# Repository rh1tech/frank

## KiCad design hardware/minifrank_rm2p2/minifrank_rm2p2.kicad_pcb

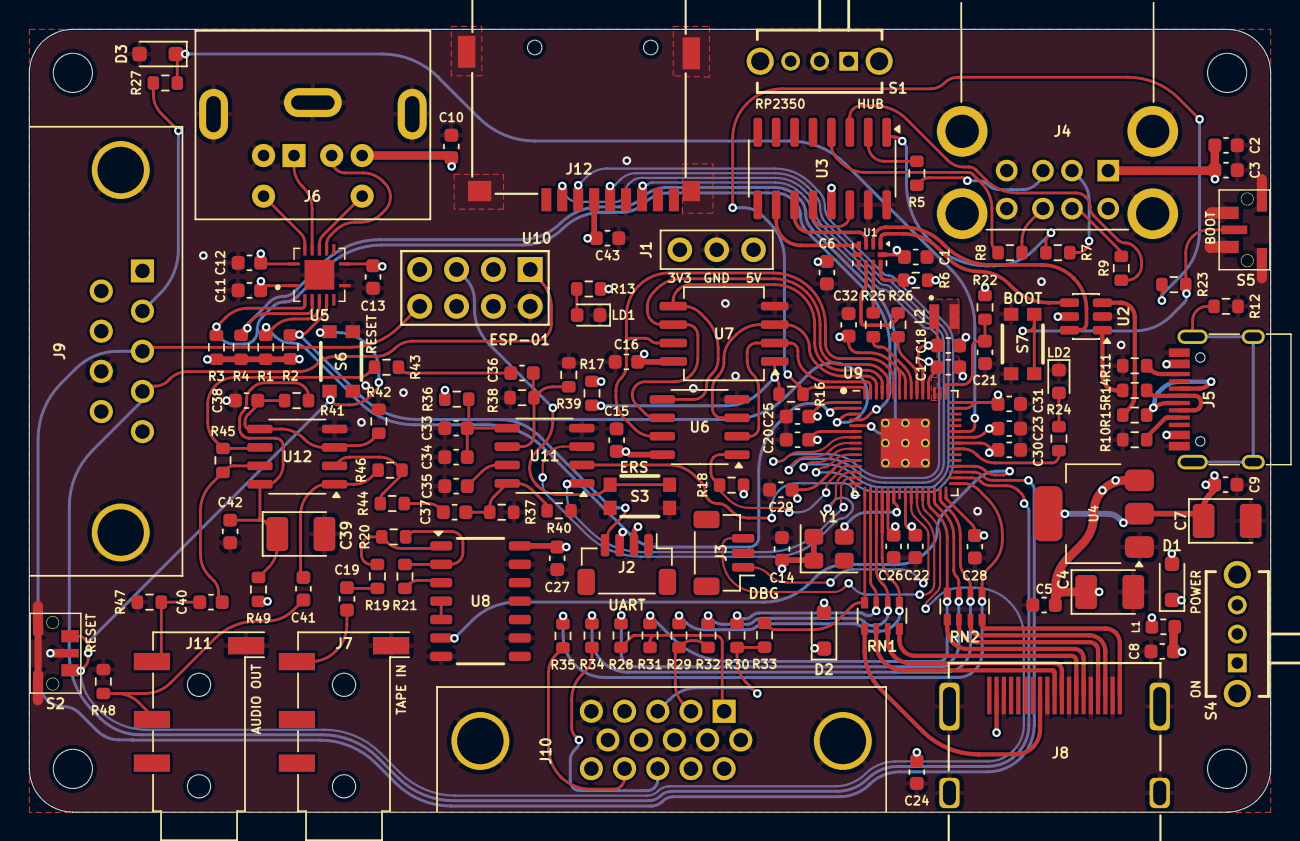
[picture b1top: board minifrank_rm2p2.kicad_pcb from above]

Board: 4 copper layers, 85.6 x 54.0 mm, 137 parts (0 on the bottom side), 113 nets.

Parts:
C1, C5, C8, C9, C10, C11, C12, C13, C14, C15, C16, C19, C20, C23, C24, C25, C26, C27, C28, C29, C30, C31, C32, C34, C42, C43: 100n; C_0603_1608Metric
C2, C3, C33, C35, C36, C37, C38, C40, C41: 10u; C_0603_1608Metric
C4, C7: 22u; Capacitor (3528, tantalum, polar)
C6, C17, C18, C21, C22: 4.7u; C_0603_1608Metric
C39: 10u; Capacitor (3528, tantalum, polar)
D1, D2: 1N5819WS; Diode (SOD-323)
D3: 3V3; Diode (SOD-323)
H1, H2, H3, H4: Hole 2.7mm; Mounting Hole (2.7mm)
J1: PWR; Pin Header (1x03)
J2: UART; JST_SH_BM04B-SRSS-TB_1x04-1MP_P1.00mm_Vertical
J3: DEBUG; JST_SH_BM03B-SRSS-TB_1x03-1MP_P1.00mm_Vertical
J4: SS-52100-004; USB Type A (stacked)
J5: USB4215-03-A; USB Type C
J6: MDC-036; MiniDIN (6 Pin, female)
J7, J11: PJ-320D; Jack (3.5mm, PJ-320D)
J8: DC3RX19JA2; HDMI (female)
J9: GP2; D-SUB (9 pin, male, top mount)
J10: VGA; D-SUB (15 pin, female)
J12: 104031-0811; MicroSD (SMD, long)
L1: 330R; L_0603_1608Metric
L2: 3.3u; L_pol_2016
LD1: Green; LED_0603_1608Metric
LD2: Blue; LED_0603_1608Metric
R1, R2, R3, R4, R6, R17, R18, R39, R40, R41, R42, R43, R44: 10K; R_0603_1608Metric
R5, R7, R8, R9, R14, R15: 22R; R_0603_1608Metric
R10, R11: 5.1K; R_0603_1608Metric
R12: 1M; R_0603_1608Metric
R13, R23, R24, R27, R31, R32, R33: 1K; R_0603_1608Metric
R16: 0R; R_0603_1608Metric
R19: 4.7K; R_0603_1608Metric
R20, R21: 100K; R_0603_1608Metric
R22: 33R; R_0603_1608Metric
R25, R26: 27R; R_0603_1608Metric
R28, R29, R30: 330R; R_0603_1608Metric
R34, R35, R36, R49: 100R; R_0603_1608Metric
R37, R38: 470R; R_0603_1608Metric
R45, R46: 47K; R_0603_1608Metric
R47, R48: 20K; R_0603_1608Metric
RN1, RN2: 270R; Resistor Array (4x0603)
S1, S4: SK12D07VG3NS
S2, S5: RP Reset; TS-1234VW
S3: ESP Reset; KMR_2
S6, S7: RP Reset; KMR_2
U1: TS3USB221RSER; UQFN-10
U2: USBLC6-2SC6; SOT-23-6
U3: MW7211A; SOP-16
U4: NCP1117-3.3_SOT223; SOT-223-3_TabPin2
U5: TXS0104ERGYR; RGY_S-PVQFN-N14_
U6: ESP-PSRAM32; SO-8
U7: W25Q128JVS; SOIC-8
U8: CD4069UBM; SOIC127P600X175-14N
U9: RP2350; QFN 60 (RP2350A)
U10: ESP-01v090; ESP-01
U11: TDA1387T; SO-8
U12: LM358; SO-8
Y1: ASE-12MHz; Oscillator_SMD_Abracon_ASE-4Pin_3.2x2.5mm

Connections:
+1V1: C18.1, C20.1, C22.1, C23.1, L2.1, U9.6 (DVDD), U9.23 (DVDD), U9.39 (DVDD), U9.50 (VREG_FB)
+3V3: C1.2, C7.1, C9.2, C11.1, C13.1, C14.1, C15.1, C16.1, C17.1, C25.1, C26.1, C27.1, C28.1, C29.1, C30.1, C31.1, C32.1, C43.2, J1.1, J2.2, J12.4 (VDD), R1.2, R2.2, R3.2, R4.2, R6.1, R13.2, R17.1, R18.2, R22.1, U1.10 (VCC), U4.2 (VO), U5.1 (VCCA), U5.8 (OE), U6.8 (VCC), U7.8 (VCC), U8.14 (VDD), U9.1 (IOVDD), U9.11 (IOVDD), U9.20 (IOVDD), U9.30 (IOVDD), U9.38 (IOVDD), U9.44 (ADC_AVDD), U9.45 (IOVDD), U9.49 (VREG_VIN), U9.53 (USB_OTP_VDD), U9.54 (QSPI_IOVDD), U10.7 (VCC), Y1.1 (EN), Y1.4 (Vdd)
/Audio/AMP_OUTL: C40.2, J11.T, R47.2
/Audio/AMP_OUTR: C41.2, J11.R, R48.2
/Audio/TDA_L: C36.1, R38.2, R39.1, U11.6 (A_LEFT)
/Audio/TDA_R: C37.1, R37.1, R40.1, U11.8 (A_RIGHT)
/D+: R25.1, U1.8 (D+)
/D-: R26.1, U1.7 (D-)
/ESP_RST: S3.2, S3.4, U10.5 (RST)
/GPIO0: J2.3, R1.1, U5.4 (A3), U9.2 (GPIO0)
/GPIO1: J2.4, R2.1, U5.5 (A4), U9.3 (GPIO1)
/GPIO2: R3.1, U5.2 (A1), U9.4 (GPIO2)
/GPIO3: R4.1, U5.3 (A2), U9.5 (GPIO3)
/GPIO4: J12.7 (DAT0), U9.7 (GPIO4)
/GPIO5: J12.2 (DAT3/CD), U9.8 (GPIO5)
/GPIO6: J12.5 (CLK), U9.9 (GPIO6)
/GPIO7: J12.3 (CMD), U9.10 (GPIO7)
/GPIO8: R18.1, U6.1 (~CE), U9.12 (GPIO8)
/GPIO9: U9.13 (GPIO9), U11.3 (DATA)
/GPIO10: U9.14 (GPIO10), U11.1 (SCLK)
/GPIO11: U9.15 (GPIO11), U11.2 (LRCK)
/GPIO12: R33.1, RN1.4 (R4.1), U9.16 (GPIO12)
/GPIO13: R30.1, RN1.3 (R3.1), U9.17 (GPIO13)
/GPIO14: R32.1, RN1.2 (R2.1), U9.18 (GPIO14)
/GPIO15: R29.1, RN1.1 (R1.1), U9.19 (GPIO15)
/GPIO16: R31.1, RN2.4 (R4.1), U9.27 (GPIO16)
/GPIO17: R28.1, RN2.3 (R3.1), U9.28 (GPIO17)
/GPIO18: R34.2, RN2.2 (R2.1), U9.29 (GPIO18)
/GPIO19: R35.2, RN2.1 (R1.1), U9.31 (GPIO19)
/GPIO20: J9.4, U9.32 (GPIO20), U10.1 (UTXD)
/GPIO21: J9.3, U9.33 (GPIO21), U10.8 (URXD)
/GPIO22: U8.6 (I=*C), U9.34 (GPIO22)
/GPIO26: D3.1 (K), R27.1, U9.40 (GPIO26_ADC0)
/PS2/KB_CLK_5V: J6.5, U5.13 (B1)
/PS2/KB_DATA_5V: J6.1, U5.12 (B2)
/PS2/MS_CLK_5V: J6.6, U5.11 (B3)
/PS2/MS_DATA_5V: J6.2, U5.10 (B4)
/Power/D1+: U1.1 (1D+), U2.4 (I/O2)
/Power/D1-: U1.2 (1D-), U2.6 (I/O1)
/Power/D2+: U1.3 (2D+), U3.11 (DPU)
/Power/D2-: U1.4 (2D-), U3.10 (DMU)
/Power/DS1+: R5.1, U3.2 (DP0)
/Power/DS1-: R7.1, U3.1 (DM0)
/Power/DS2+: R8.1, U3.4 (DP1)
/Power/DS2-: R9.1, U3.3 (DM1)
/Power/VBUS_IN: D1.1 (K), S4.2
/RP2350A/FLASH_SS: R16.2, R17.2, U7.1 (~CS)
/RP2350A/QSPI_SCLK: U6.6 (SCLK), U7.6 (CLK), U9.56 (QSPI_SCLK)
/RP2350A/QSPI_SD0: U6.5 (SI/SIO), U7.5 (DI(IO0)), U9.57 (QSPI_SD0)
/RP2350A/QSPI_SD1: U6.2 (SO/SIO), U7.2 (DO(IO1)), U9.59 (QSPI_SD1)
/RP2350A/QSPI_SD2: U6.3 (SIO2), U7.3 (IO2), U9.58 (QSPI_SD2)
/RP2350A/QSPI_SD3: U6.7 (SIO3), U7.7 (IO3), U9.55 (QSPI_SD3)
/RP2350A/QSPI_SS: R16.1, R23.1, U9.60 (QSPI_SS)
/RP2350A/VREG_AVDD: C21.1, R22.2, U9.46 (VREG_AVDD)
/RP2350A/VREG_LX: L2.2, U9.48 (VREG_LX)
/RP2350A/XIN: U9.21 (XIN), Y1.3 (OUT)
/RP2350A/~USB_BOOT: R23.2, S5.2, S7.2, S7.4
/RUN: S2.1, S6.2, S6.4, U9.26 (RUN)
/SWCLK: J3.1, U9.24 (SWCLK)
/SWD: J3.3, U9.25 (SWD)
/Tape In/TAPE: C19.2, J7.T
/USBSW: R6.2, S1.3, U1.9 (S)
GND: C1.1, C2.2, C3.2, C4.2, C5.1, C6.2, C7.2, C8.2, C9.1, C10.2, C11.2, C12.2, C13.2, C14.2, C15.2, C16.2, C17.2, C18.2, C20.2, C21.2, C22.2, C23.2, C24.2, C25.2, C26.2, C27.2, C28.2, C29.2, C30.2, C31.2, C32.2, C33.2, C34.2, C35.2, C38.1, C39.2, C42.1, C43.1, D3.2 (A), J1.2, J2.1, J3.2, J4.4 (GND1), J4.8 (GND2), J4.9 (Shield), J5.1 (GND), J5.12 (GND), J6.3, J7.S, J8.2 (G_D2), J8.5 (G_D1), J8.8 (G_D0), J8.11 (G_CLK), J8.17 (G_DDC/CEC), J8.20 (SHIELD1), J8.21 (SHIELD2), J8.22 (SHIELD3), J8.23 (SHIELD4), J9.8, J10.0, J10.5, J10.6, J10.7, J10.8, J10.10, J11.S, J12.6 (VSS), LD1.1 (K), LD2.1 (K), R10.1, R11.1, R12.2, R37.2, R38.1, R39.2, R40.2, R42.1, R47.1, R48.1, S1.2, S2.2, S2.3 (GND), S3.1, S3.3, S5.1, S5.3 (GND), S6.1, S6.3, S7.1, S7.3, U1.5 (GND), U1.6 (~OE), U2.2 (GND), U3.15 (GND), U3.16 (GND), U4.1 (GND), U5.7 (GND), U5.15 (THERMAL_PAD), U6.4 (VSS), U7.4 (GND), U8.7 (VSS), U8.9 (D14), U8.11 (E), U8.13 (F), U9.47 (VREG_PGND), U9.61 (GND), U10.2 (GND), U11.4 (AGND), U12.4 (V-), Y1.2 (GND)
GPIO25: R24.2, U9.37 (GPIO25)
unnamed: C8.1, L1.2, S4.1
unnamed: C19.1, R19.2
unnamed: C36.2, R43.2
unnamed: C37.2, R44.2
unnamed: C40.1, R45.1, U12.7
unnamed: C41.1, R46.1, U12.1
unnamed: D1.2 (A), J5.2 (VBUS), J5.11 (VBUS)
unnamed: C24.1, D2.1 (K), J8.18 (+5V)
unnamed: J4.3 (D1+), R5.2
unnamed: J4.2 (D1-), R7.2
unnamed: J4.7 (D2+), R8.2
unnamed: J4.6 (D2-), R9.2
unnamed: J5.4 (CC1), R10.2
unnamed: J5.10 (CC2), R11.2
unnamed: J5.5 (DN2), J5.7 (DN1), R14.2
unnamed: J5.6 (DP1), J5.8 (DP2), R15.2
unnamed: J5.13 (SHIELD), R12.1
unnamed: J8.12 (CLKN), RN1.5 (R4.2)
unnamed: J8.10 (CLKP), RN1.6 (R3.2)
unnamed: J8.9 (D0N), RN1.7 (R2.2)
unnamed: J8.7 (D0P), RN1.8 (R1.2)
unnamed: J8.6 (D1N), RN2.5 (R4.2)
unnamed: J8.4 (D1P), RN2.6 (R3.2)
unnamed: J8.3 (D2N), RN2.7 (R2.2)
unnamed: J8.1 (D2P), RN2.8 (R1.2)
unnamed: J9.2, R27.2
unnamed: J10.1, R28.2, R31.2
unnamed: J10.2, R29.2, R32.2
unnamed: J10.3, R30.2, R33.2
unnamed: J10.13, R34.1
unnamed: J10.14, R35.1
unnamed: LD1.2 (A), R13.1
unnamed: LD2.2 (A), R24.1
unnamed: R14.1, U2.1 (I/O1)
unnamed: R15.1, U2.3 (I/O2)
unnamed: U3.12 (VD33), U3.14 (VD3)
unnamed: R19.1, R20.2, U8.1 (A)
unnamed: R21.1, U8.3 (B)
unnamed: U8.4 (H=*B), U8.5 (C)
unnamed: R20.1, R21.2, U8.2 (G-*A)
unnamed: R26.2, U9.51 (USB_DM)
unnamed: R25.2, U9.52 (USB_DP)
unnamed: C35.1, U11.7 (FLT)
unnamed: C33.1, C34.1, R36.1, U11.5 (VA)
unnamed: C38.2, R41.1, R42.2, U12.3 (+), U12.5 (+)
unnamed: R44.1, R46.2, U12.2 (-)
unnamed: R43.1, R45.2, U12.6 (-)
unnamed: C39.1, C42.2, R41.2, R49.2, U12.8 (V+)
VBUS: C2.1, C3.1, C4.1, C5.2, C6.1, C10.1, C12.1, D2.2 (A), J1.3, J4.1 (VBUS1), J4.5 (VBUS2), J6.4, J9.6, L1.1, R36.2, R49.1, U2.5 (VBUS), U3.13 (VDD5), U4.3 (VI), U5.14 (VCCB)

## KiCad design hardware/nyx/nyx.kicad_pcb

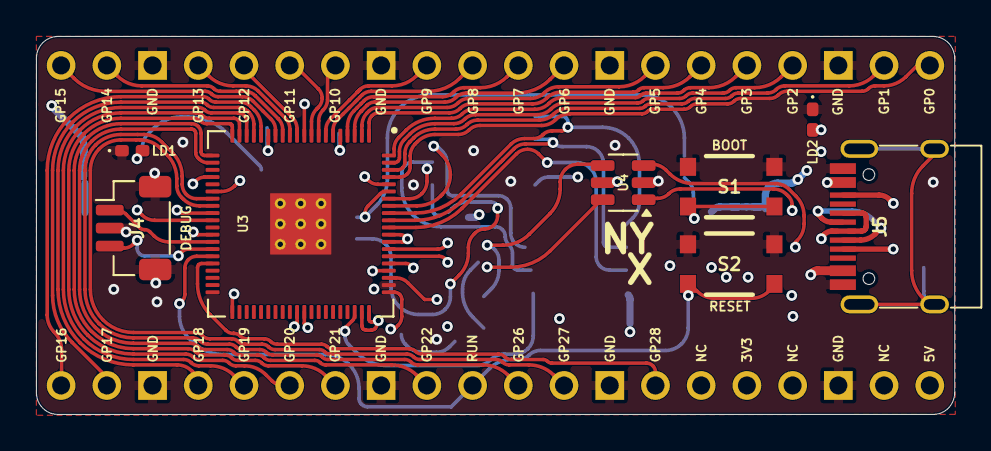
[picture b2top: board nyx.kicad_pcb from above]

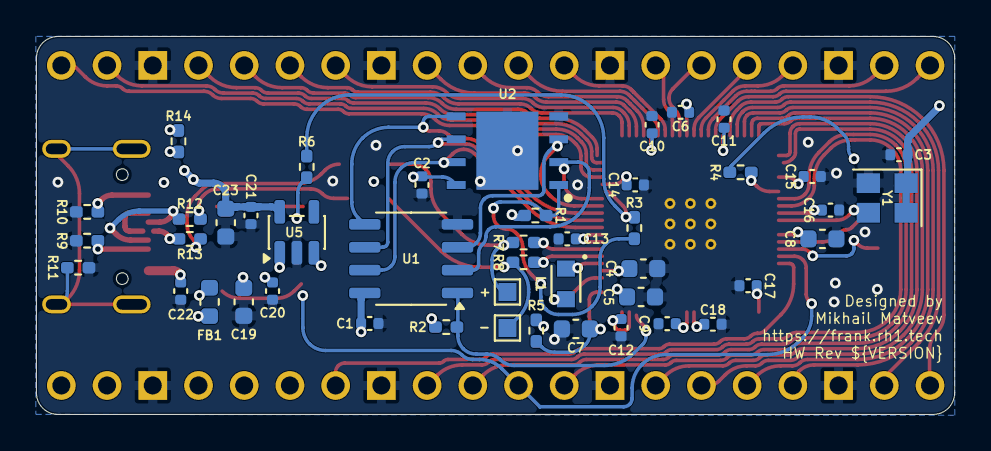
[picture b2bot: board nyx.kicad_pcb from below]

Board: 4 copper layers, 51.0 x 21.0 mm, 54 parts (44 on the bottom side), 61 nets.

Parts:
C1, C2, C3, C6, C9, C10, C11, C12, C13, C14, C15, C16, C17, C18, C20, C21, C22: 100n; C_0402_1005Metric
C4, C5, C7, C8: 4.7u; C_0603_1608Metric
C19, C23: 10u; C_0603_1608Metric
FB1: 330R; L_0603_1608Metric
J1: CON_PICO_21-40
J2: TestPoint_Pad_1.0x1.0mm_x2
J3: CON_PICO_1-20
J4: Debug; JST_SH_1x03_P1.00mm_Vertical
J5: USB4215-03-A; USB_C_Receptacle
L1: 3.3u; L_LQH2MCN100K02L
LD1: Blue; LED_0402_1005Metric
LD2: Green; LED_0402_1005Metric
R1, R2: 10K; R_0402_1005Metric
R3: 0R; R_0402_1005Metric
R4, R6, R14: 1K; R_0402_1005Metric
R5: 33R; R_0402_1005Metric
R7, R8: 27R; R_0402_1005Metric
R9, R10: 5.1K; R_0402_1005Metric
R11: 1M; R_0402_1005Metric
R12, R13: 22R; R_0402_1005Metric
S1: Boot; Button_SMD_3x4x2mm
S2: RP Reset; Button_SMD_3x4x2mm
U1: ESP-PSRAM64; SO-8_3.9x4.9mm_P1.27mm
U2: W25Q128JVPIQ; SON127P600X500X80-9N-D
U3: RP2350B; RP2350-QFN-80_10x10_P0.4mm
U4: USBLC6-2SC6; SOT-23-6
U5: ME6211C33M5; SOT-23-5
Y1: ASE-12MHz; Oscillator_SMD_3225_4Pin

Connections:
+1V1: C5.1, C6.1, C8.1, C9.1, L1.1, U3.10 (DVDD), U3.32 (DVDD), U3.51 (DVDD), U3.65 (VREG_FB)
+3V3: C1.1, C2.1, C3.1, C4.1, C10.1, C11.1, C12.1, C13.1, C14.1, C15.1, C16.1, C17.1, C18.1, C21.1, C23.1, J1.36, R1.2, R2.2, R5.1, R14.2, U1.8 (VCC), U2.8 (VCC), U3.5 (IOVDD), U3.15 (IOVDD), U3.24 (IOVDD), U3.29 (IOVDD), U3.41 (IOVDD), U3.50 (IOVDD), U3.59 (ADC_AVDD), U3.60 (IOVDD), U3.64 (VREG_VIN), U3.68 (USB_OTP_VDD), U3.69 (QSPI_IOVDD), U3.76 (IOVDD), U5.5 (V_{OUT}), Y1.1 (EN), Y1.4 (Vdd)
/D+: J2.1, R7.1, U4.4 (I/O2)
/D-: J2.2, R8.1, U4.6 (I/O1)
/GPIO0: J3.1, U3.77 (GPIO0)
/GPIO1: J3.2, U3.78 (GPIO1)
/GPIO2: J3.4, U3.79 (GPIO2)
/GPIO3: J3.5, U3.80 (GPIO3)
/GPIO4: J3.6, U3.1 (GPIO4)
/GPIO5: J3.7, U3.2 (GPIO5)
/GPIO6: J3.9, U3.3 (GPIO6)
/GPIO7: J3.10, U3.4 (GPIO7)
/GPIO8: J3.11, U3.6 (GPIO8)
/GPIO9: J3.12, U3.7 (GPIO9)
/GPIO10: J3.14, U3.8 (GPIO10)
/GPIO11: J3.15, U3.9 (GPIO11)
/GPIO12: J3.16, U3.11 (GPIO12)
/GPIO13: J3.17, U3.12 (GPIO13)
/GPIO14: J3.19, U3.13 (GPIO14)
/GPIO15: J3.20, U3.14 (GPIO15)
/GPIO16: J1.21, U3.16 (GPIO16)
/GPIO17: J1.22, U3.17 (GPIO17)
/GPIO18: J1.24, U3.18 (GPIO18)
/GPIO19: J1.25, U3.19 (GPIO19)
/GPIO20: J1.26, U3.20 (GPIO20)
/GPIO21: J1.27, U3.21 (GPIO21)
/GPIO22: J1.29, U3.22 (GPIO22)
/GPIO26: J1.31, U3.27 (GPIO26)
/GPIO27: J1.32, U3.28 (GPIO27)
/GPIO28: J1.34, U3.36 (GPIO28)
/Power/VBUS_IN: C22.1, FB1.1, J5.2 (VBUS), J5.11 (VBUS)
/RP2350B/GPIO47: R2.1, U1.1 (~CE), U3.58 (GPIO47_ADC7)
/RP2350B/QSPI_SCLK: U1.6 (SCLK), U2.6 (CLK), U3.71 (QSPI_SCLK)
/RP2350B/QSPI_SD0: U1.5 (SI/SIO), U2.5 (DI_(IO0)), U3.72 (QSPI_SD0)
/RP2350B/QSPI_SD1: U1.2 (SO/SIO), U2.2 (DO_(IO1)), U3.74 (QSPI_SD1)
/RP2350B/QSPI_SD2: U1.3 (SIO2), U2.3 (~WP_(IO2)), U3.73 (QSPI_SD2)
/RP2350B/QSPI_SD3: U1.7 (SIO3), U2.7 (~HOLD_OR_/RESET_(IO3)), U3.70 (QSPI_SD3)
/RP2350B/QSPI_SS: R3.1, R6.1, U3.75 (QSPI_SS)
/RP2350B/SWCLK: J4.3, U3.33 (SWCLK)
/RP2350B/SWD: J4.1, U3.34 (SWD)
/RP2350B/VREG_AVDD: C7.1, R5.2, U3.61 (VREG_AVDD)
/RP2350B/VREG_LX: L1.2, U3.63 (VREG_LX)
/RP2350B/XIN: U3.30 (XIN), Y1.3 (OUT)
/RP2350B/~USB_BOOT: R6.2, S1.1, S1.3
/RUN: J1.30, S2.1, S2.3, U3.35 (RUN)
GND: C1.2, C2.2, C3.2, C4.2, C5.2, C6.2, C7.2, C8.2, C9.2, C10.2, C11.2, C12.2, C13.2, C14.2, C15.2, C16.2, C17.2, C18.2, C19.1, C20.1, C21.2, C22.2, C23.2, J1.23, J1.28, J1.33, J1.38, J3.3, J3.8, J3.13, J3.18, J4.2, J5.1 (GND), J5.12 (GND), LD1.1 (K), LD2.1 (K), R9.1, R10.1, R11.2, S1.2, S1.4, S2.2, S2.4, U1.4 (VSS), U2.4 (GND_1), U2.9 (GND_2), U3.62 (VREG_PGND), U3.81 (GND), U4.2 (GND), U5.2 (V_{SS}), Y1.2 (GND)
unnamed: J5.4 (CC1), R9.2
unnamed: J5.10 (CC2), R10.2
unnamed: J5.5 (DN2), J5.7 (DN1), R12.2
unnamed: J5.6 (DP1), J5.8 (DP2), R13.2
unnamed: J5.13 (SHIELD), R11.1
unnamed: LD1.2 (A), R4.1
unnamed: LD2.2 (A), R14.1
unnamed: R12.1, U4.1 (I/O1)
unnamed: R13.1, U4.3 (I/O2)
unnamed: R1.1, R3.2, U2.1 (~CS)
unnamed: R4.2, U3.26 (GPIO25)
unnamed: R8.2, U3.66 (USB_DM)
unnamed: R7.2, U3.67 (USB_DP)
unnamed: C19.2, C20.2, FB1.2, U5.1 (V_{IN}), U5.3 (CE)
VBUS: J1.40, U4.5 (VBUS)

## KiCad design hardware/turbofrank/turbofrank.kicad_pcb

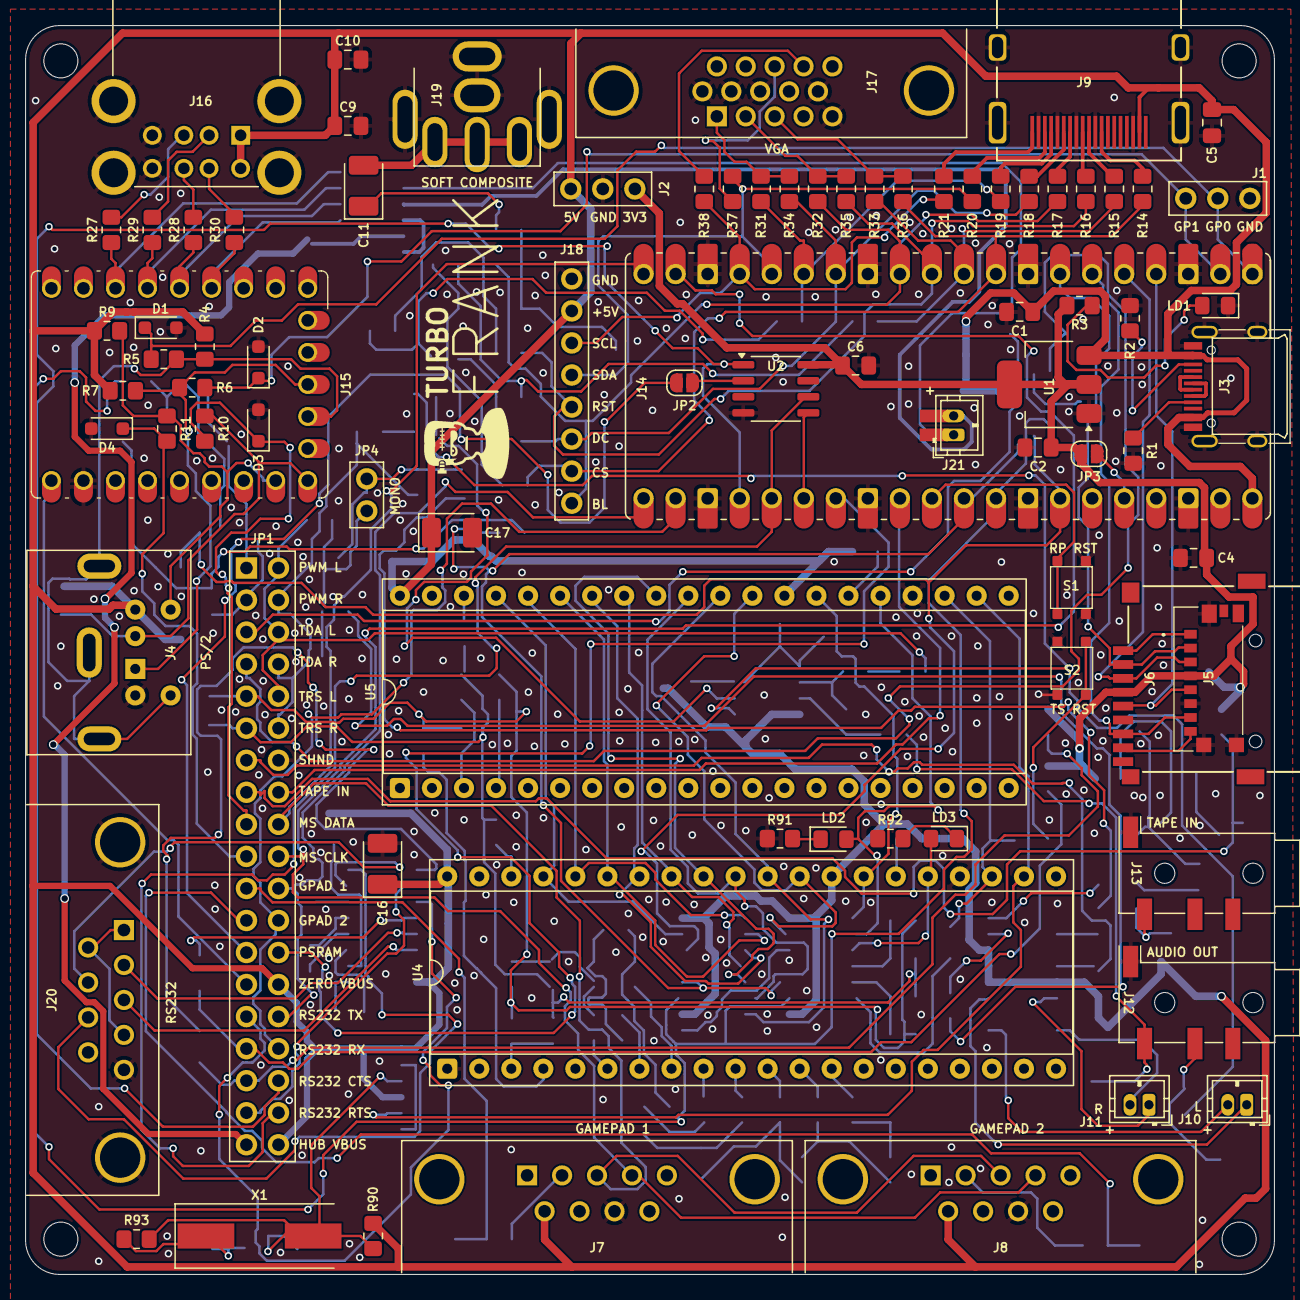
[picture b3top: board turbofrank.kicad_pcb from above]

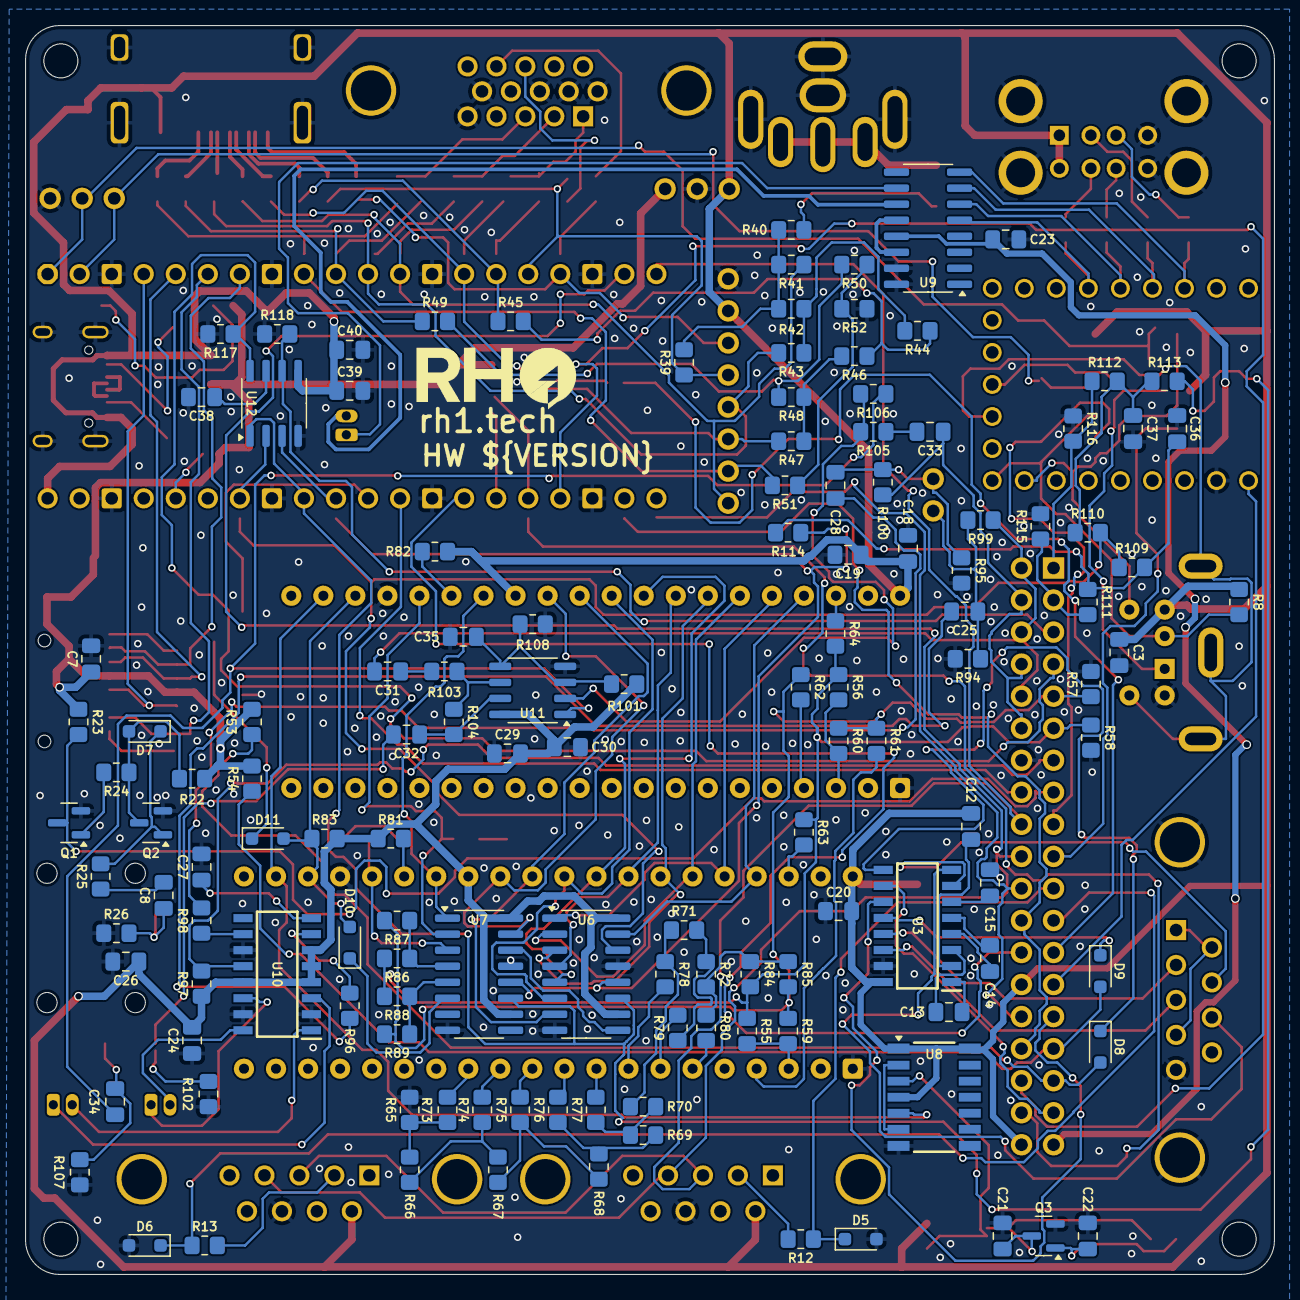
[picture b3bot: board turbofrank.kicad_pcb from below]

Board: 2 copper layers, 99.0 x 99.0 mm, 219 parts (132 on the bottom side), 187 nets.

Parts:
C1, C2, C9, C10, C29, C31, C32, C33, C34, C35, C38, C39: 10u; Capacitor (0805)
C3, C4, C5, C6, C7, C8, C18, C19, C20, C27, C30, C40: 100n; Capacitor (0805)
C11: 220u; Capacitor (3528, tantalum, polar)
C12, C13, C14, C15, C24, C25, C28: 1u; Capacitor (0805)
C16, C17: 100u; Capacitor (3528, tantalum, polar)
C21, C22: 22p; Capacitor (0805)
C23: 4.7u; Capacitor (0805)
C26: 47u; Capacitor (0805)
C36, C37: 47n; Capacitor (0805)
D1, D2, D3, D4, D5, D6: 3V3; Diode (SOD-323)
D7, D8, D9, D10, D11: 1N4148; Diode (SOD-323)
H1, H2, H3, H4: Hole 2.7mm; Mounting Hole (2.7mm)
J1: UART; Pin Header (1x03)
J2: PWR; Pin Header (1x03)
J3: USB4215; USB Type C
J4: MDC-036; MiniDIN (6 Pin, female)
J5: 0475710001; MicroSD (SMD, short)
J6: 104031-0811; MicroSD (SMD, long)
J7, J8, J20: D-SUB 9 Male; D-SUB (9 pin, male, top mount)
J9: DC3RX19JA2; HDMI (female)
J10: PAM L; Connector Female ZH 1.50mm (2 pins)
J11: PAM R; Connector Female ZH 1.50mm (2 pins)
J12, J13: PJ-320D; Jack (3.5mm, PJ-320D)
J14: Rasberry Pi Pico; Raspberry Pi Pico
J15: RP2040-Zero; Raspberry Pi Zero
J16: SS-52100-004; USB Type A (stacked)
J17: D-SUB 15 Female; D-SUB (15 pin, female)
J18: Pin Header 1x08; Pin Header (1x08)
J19: RCA-103; RCA
J21: USB HUB Data; Connector Female ZH 1.50mm (2 pins + tracks)
JP1: Main Jumper Set; Pin Header (2x19)
JP2, JP3: Jumper (Solder); Jumper (solder)
JP4: Mono; Pin Header (1x02)
LD1: Green; LED (0805)
LD2, LD3: Orange; LED (0805)
Q1, Q2, Q3: BC850; SOT-23
R1, R2: 5.1K; Resistor (0805)
R3, R4, R7, R8, R9, R12, R13, R23, R34, R35, R36, R53, R54, R66, R67, R68, R69, R70, R71, R72, R81, R82, R90, R91, R92, R113, R114: 1K; Resistor (0805)
R5, R6, R10, R11, R26, R37, R38: 100R; Resistor (0805)
R14, R15, R16, R17, R18, R19, R20, R21, R41, R43, R45, R47, R49, R51: 270R; Resistor (0805)
R22, R24, R25, R83, R84, R85, R86, R87, R88, R89, R96, R97, R98, R99, R100, R101, R103, R105, R108, R111, R112: 10K; Resistor (0805)
R27, R28, R29, R30: 22R; Resistor (0805)
R31, R32, R33: 330R; Resistor (0805)
R39: 750R; Resistor (0805)
R40: 51R; Resistor (0805)
R42, R44, R46, R48, R50: 150R; Resistor (0805)
R52: 300R; Resistor (0805)
R55, R56, R61, R62, R65, R73, R74, R75, R76, R77, R78, R79, R80, R94, R95, R109, R110, R115, R116: 2K; Resistor (0805)
R57, R58: 120R; Resistor (0805)
R59, R60, R63, R64: 4.7K; Resistor (0805)
R93: 100K; Resistor (0805)
R102, R107: 20K; Resistor (0805)
R104, R106: 47K; Resistor (0805)
R117, R118: 470R; Resistor (0805)
S1: TS-1233; Button (SMD, 3x3mm, 1-1)
S2: KLS7-TS3302; Button (SMD, 3x3mm, 1-1)
U1: NCP1117 3.3; SOT-223
U2: ESP-PSRAM32; SO-8
U3: MAX232CSE+; SOIC127P600X175-16N
U4, U5: JFC95101; DIP-40 (Socket)
U6, U7: 74HC595; SOP-16
U8: 74HC74; 74HCT74D
U9: MW7211A; SOP-16
U10: PAM8403D; SOIC127P600X175-16N
U11: LM358; SO-8
U12: TDA1387T; SO-8
X1: 3.58 MHz; Crystal (HC49-S)

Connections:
+3V3: C2.1, C4.2, C6.1, C7.1, J2.1, J5.P4 (VDD), J6.4 (VDD), JP3.2 (B), R3.2, R22.1, R23.1, R53.2, R54.2, U1.2 (VO), U2.8 (VCC)
/AMP_IN_L: C31.1, JP1.2, JP1.6, JP1.10, R99.1
/AMP_IN_R: C33.1, JP1.4, JP1.8, JP1.12, R100.1
/Audio Out/AMP_OUTL: C32.2, J12.T, R102.2
/Audio Out/AMP_OUTR: C34.2, J12.R, R107.2
/Audio Out/AMP_PAM_OUTL_M: J10.2, U10.3 (-OUTL)
/Audio Out/AMP_PAM_OUTL_P: J10.1, U10.1 (+OUT_L)
/Audio Out/AMP_PAM_OUTR_M: J11.2, U10.14 (-OUT_R)
/Audio Out/AMP_PAM_OUTR_P: J11.1, U10.16 (+OUT_R)
/Audio Out/Amplifier/ MONO_L: C25.1, JP4.1, R94.1, R99.2
/Audio Out/Amplifier/MONO_R: C28.1, JP4.2, R95.1, R100.2
/Audio Out/TS/A1: R62.2, U5.4 (B)
/Audio Out/TS/A2: R61.2, U4.4 (B)
/Audio Out/TS/B1: R56.2, R60.2, U5.3 (A)
/Audio Out/TS/B2: R55.2, R59.2, U4.3 (A)
/Audio Out/TS/BEEP: R86.2, R87.2, U7.4 (QE)
/Audio Out/TS/C1: R64.2, U5.38 (C)
/Audio Out/TS/C2: R63.2, U4.38 (C)
/Audio Out/TS/CLK_1.75M: U4.22 (CLOCK), U5.22 (CLOCK), U8.5 (Q)
/Audio Out/TS/COVOX_OUT: R72.2, R80.1, R84.2, R85.2
/Audio Out/TS/DA0: U4.37 (DA0), U5.37 (DA0), U6.15 (QA)
/Audio Out/TS/DA1: U4.36 (DA1), U5.36 (DA1), U6.1 (QB)
/Audio Out/TS/DA2: U4.35 (DA2), U5.35 (DA2), U6.2 (QC)
/Audio Out/TS/DA3: U4.34 (DA3), U5.34 (DA3), U6.3 (QD)
/Audio Out/TS/DA4: U4.33 (DA4), U5.33 (DA4), U6.4 (QE)
/Audio Out/TS/DA5: U4.32 (DA5), U5.32 (DA5), U6.5 (QF)
/Audio Out/TS/DA6: U4.31 (DA6), U5.31 (DA6), U6.6 (QG)
/Audio Out/TS/DA7: U4.30 (DA7), U5.30 (DA7), U6.7 (QH)
/Audio Out/TS/DAC0: R73.2, U4.13 (IOB0)
/Audio Out/TS/DAC1: R74.2, U4.12 (IOB1)
/Audio Out/TS/DAC2: R75.2, U4.11 (IOB2)
/Audio Out/TS/DAC3: R76.2, U4.10 (IOB3)
/Audio Out/TS/DAC4: R77.2, U4.9 (IOB4)
/Audio Out/TS/DAC5: R78.2, U4.8 (IOB5)
/Audio Out/TS/DAC6: R79.2, U4.7 (IOB6)
/Audio Out/TS/DAC7: R80.2, U4.6 (IOB7)
/Audio Out/TS/SAVE: R88.2, R89.2, U7.5 (QF)
/Audio Out/TS/YM_BC1: U4.29 (BC1), U5.29 (BC1), U7.15 (QA)
/Audio Out/TS/YM_BDIR: U4.27 (BDIR), U5.27 (BDIR), U7.1 (QB)
/Audio Out/TS/YM_CS1: LD2.2 (A), U5.25 (A8), U7.2 (QC)
/Audio Out/TS/YM_CS2: LD3.2 (A), U4.25 (A8), U7.3 (QD)
/Audio Out/TS/YM_RST: D10.2 (A), D11.2 (A), R83.1, U4.23 (~RESET), U5.23 (~RESET)
/Audio Out/TS/YM_SEL1: R82.2, U5.26 (~SEL)
/Audio Out/TS/YM_SEL2: R81.2, U4.26 (~SEL)
/Composite/CVBS: C11.2, J19.1
/GP1_DATA: D5.1 (K), JP1.21, R12.1
/GP2_DATA: D6.1 (K), JP1.23, R13.1
/GPIO0: D1.1 (K), J1.2, J14.1 (GPIO0), R5.2
/GPIO1: D2.1 (K), J1.3, J14.2 (GPIO1), R6.2
/GPIO2: J5.P5 (CLK), J6.5 (CLK), J14.4 (GPIO2)
/GPIO3: J5.P3 (CMD), J6.3 (CMD), J14.5 (GPIO3)
/GPIO4: J5.P7 (DAT0), J6.7 (DAT0), J14.6 (GPIO4)
/GPIO5: J5.P2 (CD/DAT3), J6.2 (DAT3/CD), J14.7 (GPIO5)
/GPIO6: J14.9 (GPIO6), J18.7, R14.2, R36.1, R51.1
/GPIO7: J14.10 (GPIO7), R15.2, R33.1, R49.1
/GPIO8: J14.11 (GPIO8), J18.5, R16.2, R35.1, R43.1
/GPIO9: J14.12 (GPIO9), J18.8, R17.2, R32.1, R41.1
/GPIO10: J14.14 (GPIO10), J18.6, R18.2, R34.1, R47.1
/GPIO11: J14.15 (GPIO11), R19.2, R31.1, R45.1
/GPIO12: J14.16 (GPIO12), J18.4, R20.2, R37.2, R39.1
/GPIO13: J14.17 (GPIO13), J18.3, R21.2, R38.2
/GPIO14: J7.4, J8.4, J14.19 (GPIO14), JP1.20
/GPIO15: J7.3, J8.3, J14.20 (GPIO15), JP1.18
/GPIO16: J14.21 (GPIO16), JP1.22, JP1.30
/GPIO17: J14.22 (GPIO17), JP1.24, JP1.32
/GPIO18: J14.24 (GPIO18), JP1.34, U2.1 (~CE)
/GPIO19: J14.25 (GPIO19), JP1.36, U2.6 (SCLK)
/GPIO20: J14.26 (GPIO20), U2.5 (SI/SIO)
/GPIO21: J14.27 (GPIO21), JP1.26
/GPIO22: J14.29 (GPIO22), JP1.16
/GPIO26: J14.31 (GPIO26_ADC0), R114.2, U6.12 (RCLK), U7.12 (RCLK), U12.3 (DATA)
/GPIO27: J14.32 (GPIO27_ADC1), R113.2, U6.11 (SRCLK), U7.11 (SRCLK), U12.1 (SCLK)
/GPIO28: J14.34 (GPIO28_ADC2), R109.1, R110.1, U6.14 (SER), U12.2 (LRCK)
/KB_CLK: J4.5, J15.13 (12), R4.2, R5.1
/KB_DATA: J4.1, J15.12 (11), R6.1, R7.2
/LOAD_IN_D: JP1.15, Q1.3 (C), R23.2
/MS_CLK: J4.6, J15.16 (15), R9.2, R11.1
/MS_CLK_3V: D4.1 (K), JP1.19, R11.2
/MS_DATA: J4.2, J15.15 (14), R8.2, R10.1
/MS_DATA_3V: D3.1 (K), JP1.17, R10.2
/Micro SD/DAT1: J5.P8 (DAT1), J6.8 (DAT1)
/Micro SD/DAT2: J5.P1 (DAT2), J6.1 (DAT2)
/PSR_SOSIO: JP1.25, JP2.2 (B)
/PWM_OUT_L: JP1.1, R112.2, R116.1
/PWM_OUT_R: JP1.3, R111.2, R115.1
/Power/D+: J3.6 (DP1), J3.8 (DP2)
/Power/D-: J3.5 (DN2), J3.7 (DN1)
/RS232/C1+: C13.2, U3.1 (C1+)
/RS232/C1-: C13.1, U3.3 (C1-)
/RS232/C2+: C14.2, U3.4 (C2+)
/RS232/C2-: C14.1, U3.5 (C2-)
/RS232/CTS_IN: J20.7, U3.7 (T2OUT)
/RS232/CTS_MAX: D8.1 (K), U3.9 (R2OUT)
/RS232/RTS_IN: J20.8, U3.8 (R2IN)
/RS232/RX_IN: J20.3, U3.14 (T1OUT)
/RS232/RX_MAX: D9.1 (K), U3.12 (R1OUT)
/RS232/TX_IN: J20.2, U3.13 (R1IN)
/RS232/V+: C12.1, U3.2 (V+)
/RS232/V-: C15.1, U3.6 (V-)
/RS232_CTS: D8.2 (A), JP1.33, R53.1
/RS232_RTS: JP1.35, U3.10 (T2IN)
/RS232_RX: D9.2 (A), JP1.31, R54.1
/RS232_TX: JP1.29, U3.11 (T1IN)
/RUN: J14.30 (RUN), S1.1
/SHND: JP1.13, R97.2, U10.12 (SHND)
/TDA_L: JP1.5, R118.2, U12.6 (A_LEFT)
/TDA_R: JP1.7, R117.1, U12.8 (A_RIGHT)
/TS_L: JP1.9, R57.1, R59.1, R60.1, R61.1, R62.1, R85.1, R87.1, R89.1
/TS_R: JP1.11, R55.1, R56.1, R58.1, R63.1, R64.1, R84.1, R86.1, R88.1
/USB Hub/DM_IN: J21.2, U9.10 (DMU)
/USB Hub/DP_IN: J21.1, U9.11 (DPU)
/USBH_VBUS: C23.1, JP1.37, U9.13 (VDD5)
/USB_D1M: J15.4 (3), R29.1, U9.7 (DM3)
/USB_D1P: J15.3 (2), R27.1, U9.8 (DP3)
/USB_D2M: J15.6 (5), R30.1, U9.5 (DM2)
/USB_D2P: J15.5 (4), R28.1, U9.6 (DP2)
/ZERO_VBUS: J15.23 (5V), JP1.27
GND: C1.2, C2.2, C3.2, C4.1, C5.2, C6.2, C7.2, C9.2, C10.2, C15.2, C16.2, C17.2, C18.2, C19.2, C20.2, C21.1, C22.1, C23.2, C24.2, C26.2, C27.2, C29.1, C30.1, C35.1, C36.2, C37.2, C38.2, C39.2, C40.2, D1.2 (A), D2.2 (A), D3.2 (A), D4.2 (A), D5.2 (A), D6.2 (A), J1.1, J2.2, J3.1 (GND), J3.12 (GND), J3.13 (SHIELD), J4.3, J5.G1 (GND_1), J5.G2 (GND_2), J5.G3 (GND_3), J5.P6 (VSS), J6.6 (VSS), J7.8, J8.8, J9.2 (G_D2), J9.5 (G_D1), J9.8 (G_D0), J9.11 (G_CLK), J9.17 (G_DDC/CEC), J9.20 (SHIELD1), J9.21 (SHIELD2), J9.22 (SHIELD3), J9.23 (SHIELD4), J12.S, J13.S, J14.3 (GND), J14.8 (GND), J14.13 (GND), J14.18 (GND), J14.23 (GND), J14.28 (GND), J14.33 (AGND), J14.38 (GND), J15.22 (GND), J16.4 (GND1), J16.8 (GND2), J16.9 (Shield), J17.0, J17.5, J17.6, J17.7, J17.8, J17.10, J18.1, J19.2, J20.5, JP1.14, LD1.1 (K), Q1.2 (E), Q2.2 (E), Q3.2 (E), R1.1, R2.1, R26.2, R52.1, R57.2, R58.2, R65.1, R91.1, R92.1, R94.2, R95.2, R102.1, R107.1, R108.1, R115.2, R116.2, R117.2, R118.1, S1.2, S2.2, U1.1 (GND), U2.4 (VSS), U3.15 (GND), U4.1 (VSS), U4.24 (~A9), U5.1 (VSS), U5.24 (~A9), U6.8 (GND), U6.13 (~OE), U7.8 (GND), U7.13 (~OE), U8.7 (GND), U9.15 (GND), U9.16 (GND), U10.2 (PGND), U10.11 (GND), U10.15 (PGND), U11.4 (V-), U12.4 (AGND)
unnamed: C8.1, J13.T, R26.1
unnamed: C8.2, R25.1
unnamed: C11.1, R40.2
unnamed: C25.2, R96.2
unnamed: C28.2, R98.2
unnamed: C31.2, R103.2
unnamed: C32.1, R104.1, U11.7
unnamed: C33.2, R105.2
unnamed: C34.1, R106.1, U11.1
unnamed: C36.1, R109.2, R111.1, R114.1
unnamed: C37.1, R110.2, R112.1, R113.1
unnamed: D7.2 (A), Q2.3 (C), R22.2, R24.1
unnamed: D7.1 (K), Q2.1 (B), R25.2
unnamed: D10.1 (K), U7.6 (QG)
unnamed: D11.1 (K), S2.1
unnamed: J3.4 (CC1), R1.2
unnamed: J3.10 (CC2), R2.2
unnamed: J7.2, R12.2
unnamed: J8.2, R13.2
unnamed: J9.12 (CLKN), R14.1
unnamed: J9.10 (CLKP), R15.1
unnamed: J9.9 (D0N), R16.1
unnamed: J9.7 (D0P), R17.1
unnamed: J9.6 (D1N), R18.1
unnamed: J9.4 (D1P), R19.1
unnamed: J9.3 (D2N), R20.1
unnamed: J9.1 (D2P), R21.1
unnamed: J14.36 (3V3), JP3.1 (A)
unnamed: J16.3 (D1+), R27.2
unnamed: J16.2 (D1-), R29.2
unnamed: J16.7 (D2+), R28.2
unnamed: J16.6 (D2-), R30.2
unnamed: J17.1, R31.2, R34.2
unnamed: J17.2, R32.2, R35.2
unnamed: J17.3, R33.2, R36.2
unnamed: J17.13, R37.1
unnamed: J17.14, R38.1
unnamed: J20.1, J20.4, J20.6
unnamed: JP2.1 (A), U2.2 (SO/SIO)
unnamed: LD1.2 (A), R3.1
unnamed: LD2.1 (K), R91.2
unnamed: LD3.1 (K), R92.2
unnamed: Q1.1 (B), R24.2
unnamed: C22.2, Q3.1 (B), R93.1, X1.1
unnamed: C21.2, Q3.3 (C), R90.1, R93.2, U8.3 (C), X1.2
unnamed: R39.2, R40.1, R41.2, R42.2
unnamed: R42.1, R43.2, R44.2
unnamed: R44.1, R45.2, R46.2
unnamed: R46.1, R47.2, R48.2
unnamed: R48.1, R49.2, R50.2
unnamed: R50.1, R51.2, R52.2
unnamed: R65.2, R66.1, R73.1
unnamed: R66.2, R67.1, R74.1
unnamed: R67.2, R68.1, R75.1
unnamed: R68.2, R69.1, R76.1
unnamed: R69.2, R70.1, R77.1
unnamed: R70.2, R71.1, R78.1
unnamed: R71.2, R72.1, R79.1
unnamed: U6.9 (QH'), U7.14 (SER)
unnamed: U8.2 (D), U8.6 (~Q)
unnamed: U9.12 (VD33), U9.14 (VD3)
unnamed: R96.1, U10.7 (INL)
unnamed: R98.1, U10.10 (INR)
unnamed: C27.1, U10.8 (VREF)
unnamed: C35.2, R101.1, R108.2, U11.3 (+), U11.5 (+)
unnamed: R105.1, R106.2, U11.2 (-)
unnamed: R103.1, R104.2, U11.6 (-)
unnamed: C38.1, U12.7 (FLT)
VBUS: C1.1, C3.1, C5.1, C9.1, C10.1, C12.2, C16.1, C17.1, C18.1, C19.1, C20.1, C24.1, C26.1, C29.2, C30.2, C39.1, C40.1, J2.3, J3.2 (VBUS), J3.11 (VBUS), J4.4, J7.6, J8.6, J9.18 (+5V), J14.40 (VBUS), J16.1 (VBUS1), J16.5 (VBUS2), J18.2, JP1.28, JP1.38, R4.1, R7.1, R8.1, R9.1, R81.1, R82.1, R83.2, R90.2, R97.1, R101.2, U1.3 (VI), U3.16 (VCC), U4.28 (BC2), U4.40 (VCC), U5.28 (BC2), U5.40 (VCC), U6.10 (~SRCLR), U6.16 (VCC), U7.10 (~SRCLR), U7.16 (VCC), U8.1 (~R), U8.4 (~S), U8.14 (VCC), U10.4 (PVDD), U10.5 (MUTE), U10.6 (VDD), U10.13 (PVDD), U11.8 (V+), U12.5 (VA)
